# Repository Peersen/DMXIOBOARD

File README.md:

# DMXIOBOARD
PCB for DMX IO from an Arduino Nano via MAX485 or SN75176 chip

### Purpose
This PCB is is designed to use an Arduino Nano to either receive(and optionally loop through) DMX or send DMX via RS485 driverchips.

### Layout
All pins of the Arduino are accesible in the 5.08 mm pitch rows in the middle of the board.
For addressing the potential DMX device a dipswitch footprint is also provided.  
The pins used for the dipswitch are also connected to the center rows as well.

### Usage

#### Hardware
As a bare minimum an arduino nano and a RS485 driver chip are needed.
The Maxim MAX485 or Texas Instruments SN75176 are pin-identical driver chips and can be used either in a DIP8 or SO8 package on the receiving or transmitting side.
Pin one is marked by a white dot on the PCB.
The dipswitch switches its input pins to ground, so pinMode(<addrPin>, INPUT_PULLUP) should be used.
As connectors footprints for a 3-pin 5.08 mm pitch screwterminal or a XLR connector are provided.
The XLR footprint is for n Neutrik NC3MD-H (male horizontal) or a NC3FD-H (female horizontal) connector.
  
#### configuring the board

##### connecting Tx/Rx
The Tx an Rx Pins of the arduino are by default NOT connected to the driver chips and therefore nothing can be send or received.
To connect the Tx/Rx pins a solder bridge or a jumper header must be soldered on the board.
This was done because having those pins connected to the driver chips prohibits uploading a sketch.

##### configuring the output
The XLR female connector and the corresponding screwterminal can be either DMX output from the arduino or passing through the dmx input.
To decide what is does two more jumperpads most be soldered. They are labeled (solder fort XLR f = DMX Through/DMXOUT".

#### Design files
The Project was done using Kicad 6.0. You`ll find a Gerber folder in the Projekt folder that should be accepted by JLCPCB.com and other manufacturers.

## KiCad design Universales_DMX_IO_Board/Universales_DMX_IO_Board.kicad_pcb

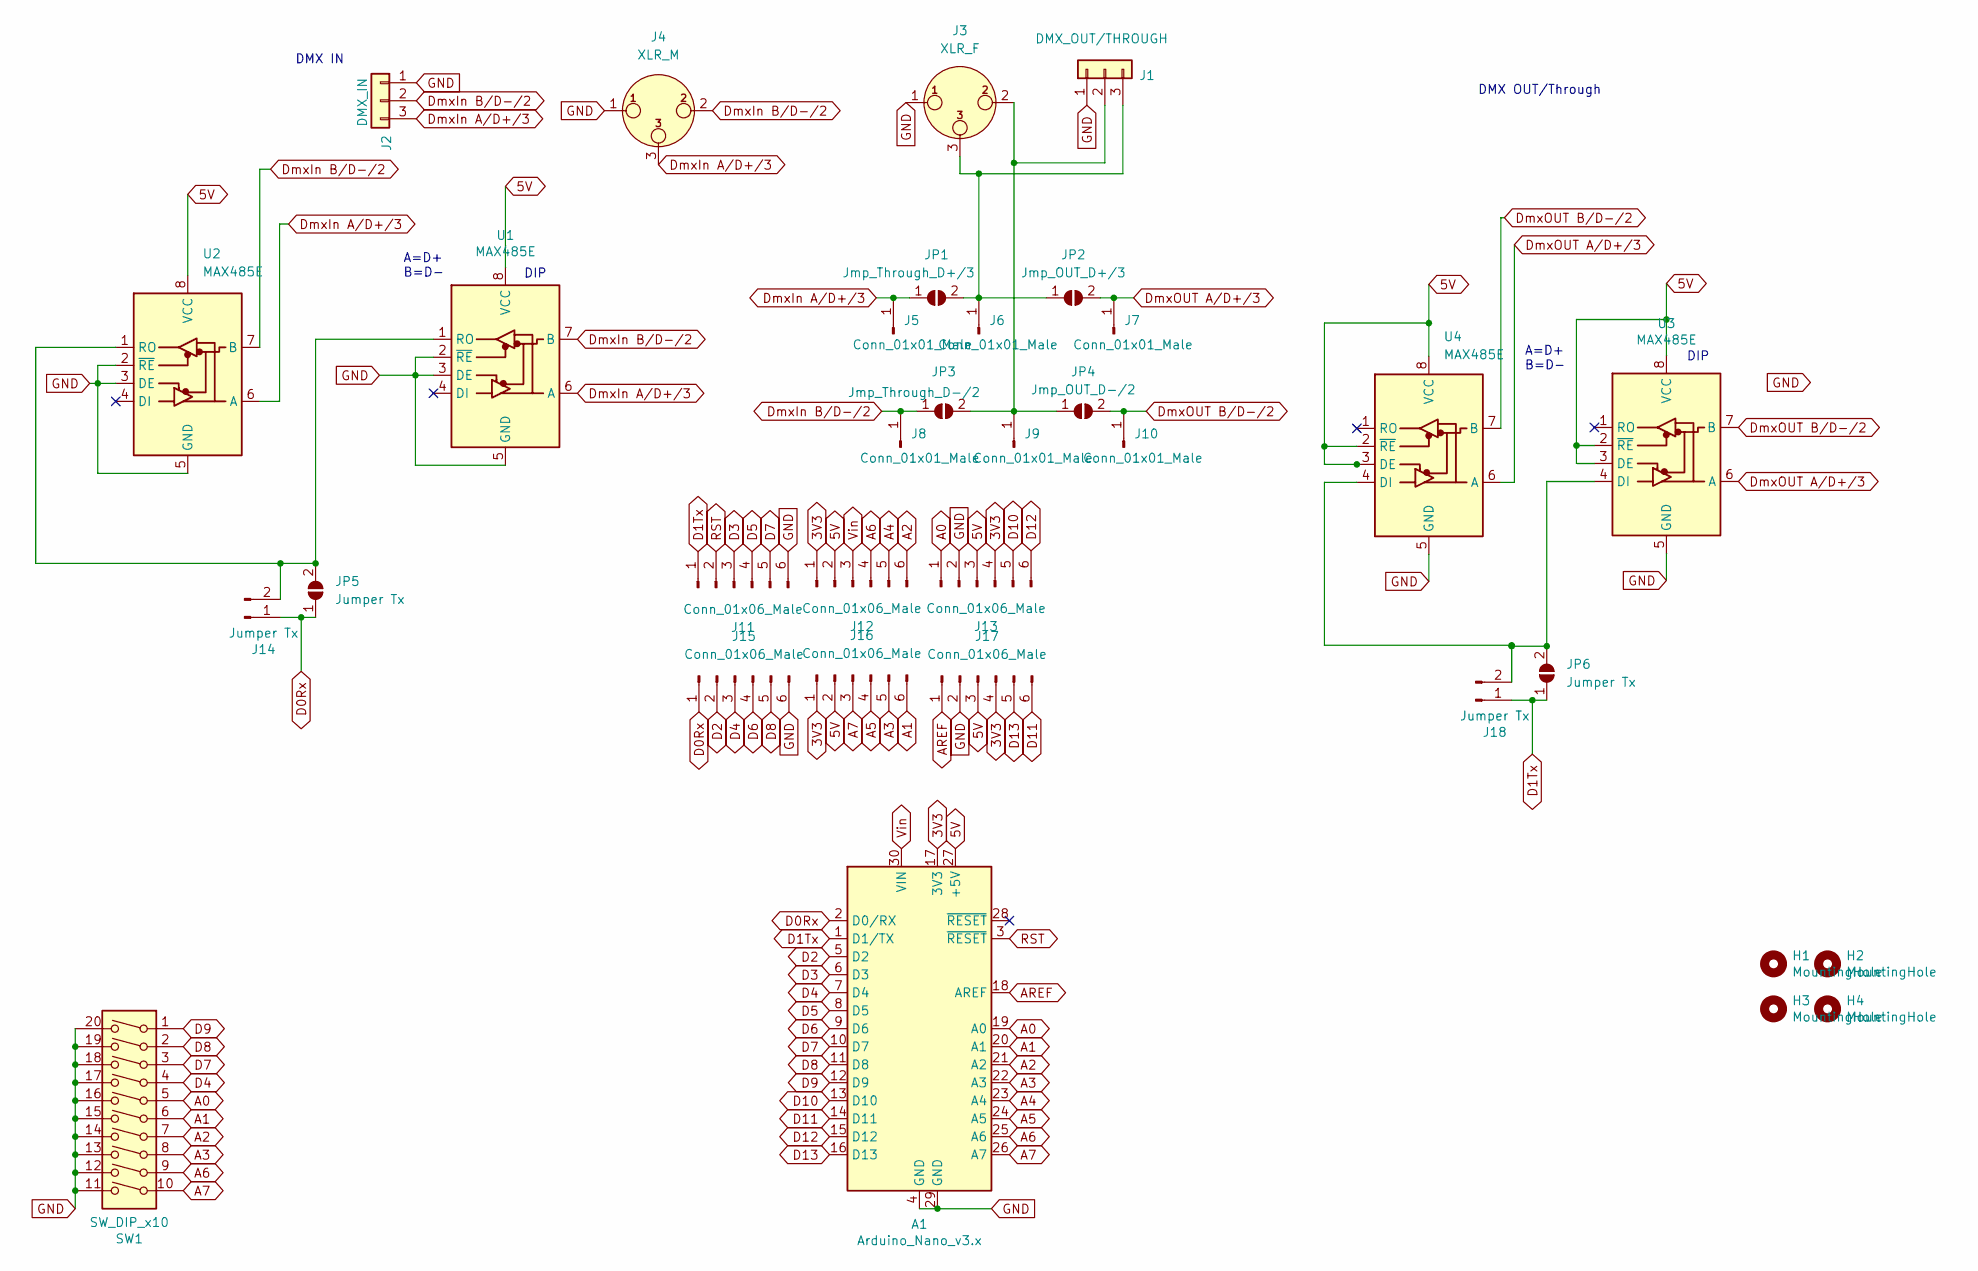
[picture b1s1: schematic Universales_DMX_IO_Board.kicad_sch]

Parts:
A1: Arduino_Nano_v3.x; Arduino_Nano_Peer_Big_Pads
H1, H2, H3, H4: MountingHole; MountingHole_3.2mm_M3_DIN965_Pad
J1: DMX_OUT/THROUGH; TerminalBlock_bornier-3_P5.08mm
J2: DMX_IN; TerminalBlock_bornier-3_P5.08mm
J3: XLR_F; Jack_XLR_Neutrik_NC3FD-H_Horizontal
J4: XLR_M; Jack_XLR_Neutrik_NC3MD-H_Horizontal
J5, J6, J7, J8, J9, J10: Conn_01x01_Male; PinHeader_1x01_P2.54mm_Vertical
J11, J12, J13, J15, J16, J17: Conn_01x06_Male; TerminalBlock_bornier-6_P5.08mm
J14, J18: Jumper Tx; PinHeader_1x02_P2.54mm_Vertical
JP1: Jmp_Through_D+/3; SolderJumper-2_P1.3mm_Open_Pad1.0x1.5mm
JP2: Jmp_OUT_D+/3; SolderJumper-2_P1.3mm_Open_Pad1.0x1.5mm
JP3: Jmp_Through_D-/2; SolderJumper-2_P1.3mm_Open_Pad1.0x1.5mm
JP4: Jmp_OUT_D-/2; SolderJumper-2_P1.3mm_Open_Pad1.0x1.5mm
JP5, JP6: Jumper Tx; SolderJumper-2_P1.3mm_Open_Pad1.0x1.5mm
SW1: SW_DIP_x10; SW_DIP_SPSTx10_Slide_9.78x27.58mm_W7.62mm_P2.54mm
U1, U3: MAX485E; SO-8_5.3x6.2mm_P1.27mm
U2, U4: MAX485E; DIP-8_W7.62mm_LongPads

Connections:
3V3: A1.17 (3V3), J12.1, J13.4, J16.1, J17.4
5V: A1.27 (+5V), J12.2, J13.3, J16.2, J17.3, U1.8 (VCC), U2.8 (VCC), U3.2 (~RE), U3.3 (DE), U3.8 (VCC), U4.2 (~RE), U4.3 (DE), U4.8 (VCC)
A0: A1.19 (A0), J13.1, SW1.5
A1: A1.20 (A1), J16.6, SW1.6
A2: A1.21 (A2), J12.6, SW1.7
A3: A1.22 (A3), J16.5, SW1.8
A4: A1.23 (A4), J12.5
A5: A1.24 (A5), J16.4
A6: A1.25 (A6), J12.4, SW1.9
A7: A1.26 (A7), J16.3, SW1.10
AREF: A1.18 (AREF), J17.1
D0Rx: A1.2 (D0/RX), J14.1, J15.1, JP5.1 (A)
D1Tx: A1.1 (D1/TX), J11.1, J18.1, JP6.1 (A)
D2: A1.5 (D2), J15.2
D3: A1.6 (D3), J11.3
D4: A1.7 (D4), J15.3, SW1.4
D5: A1.8 (D5), J11.4
D6: A1.9 (D6), J15.4
D7: A1.10 (D7), J11.5, SW1.3
D8: A1.11 (D8), J15.5, SW1.2
D9: A1.12 (D9), SW1.1
D10: A1.13 (D10), J13.5
D11: A1.14 (D11), J17.6
D12: A1.15 (D12), J13.6
D13: A1.16 (D13), J17.5
DmxIn A/D+/3: J2.3, J4.3, J5.1, JP1.1 (A), U1.6 (A), U2.6 (A)
DmxIn B/D-/2: J2.2, J4.2, J8.1, JP3.1 (A), U1.7 (B), U2.7 (B)
DmxOUT A/D+/3: J7.1, JP2.2 (B), U3.6 (A), U4.6 (A)
DmxOUT B/D-/2: J10.1, JP4.2 (B), U3.7 (B), U4.7 (B)
GND: A1.4 (GND), A1.29 (GND), J1.1, J2.1, J3.1, J4.1, J11.6, J13.2, J15.6, J17.2, SW1.11, SW1.12, SW1.13, SW1.14, SW1.15, SW1.16, SW1.17, SW1.18, SW1.19, SW1.20, U1.2 (~RE), U1.3 (DE), U1.5 (GND), U2.2 (~RE), U2.3 (DE), U2.5 (GND), U3.5 (GND), U4.5 (GND)
unnamed: J1.2, J3.2, J9.1, JP3.2 (B), JP4.1 (A)
unnamed: J1.3, J3.3, J6.1, JP1.2 (B), JP2.1 (A)
unnamed: J14.2, JP5.2 (B), U1.1 (RO), U2.1 (RO)
unnamed: J18.2, JP6.2 (B), U3.4 (DI), U4.4 (DI)
RST: A1.3 (~RESET), J11.2
Vin: A1.30 (VIN), J12.3

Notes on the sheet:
DIP
DMX IN
A=D+ B=D-
DMX OUT/Through

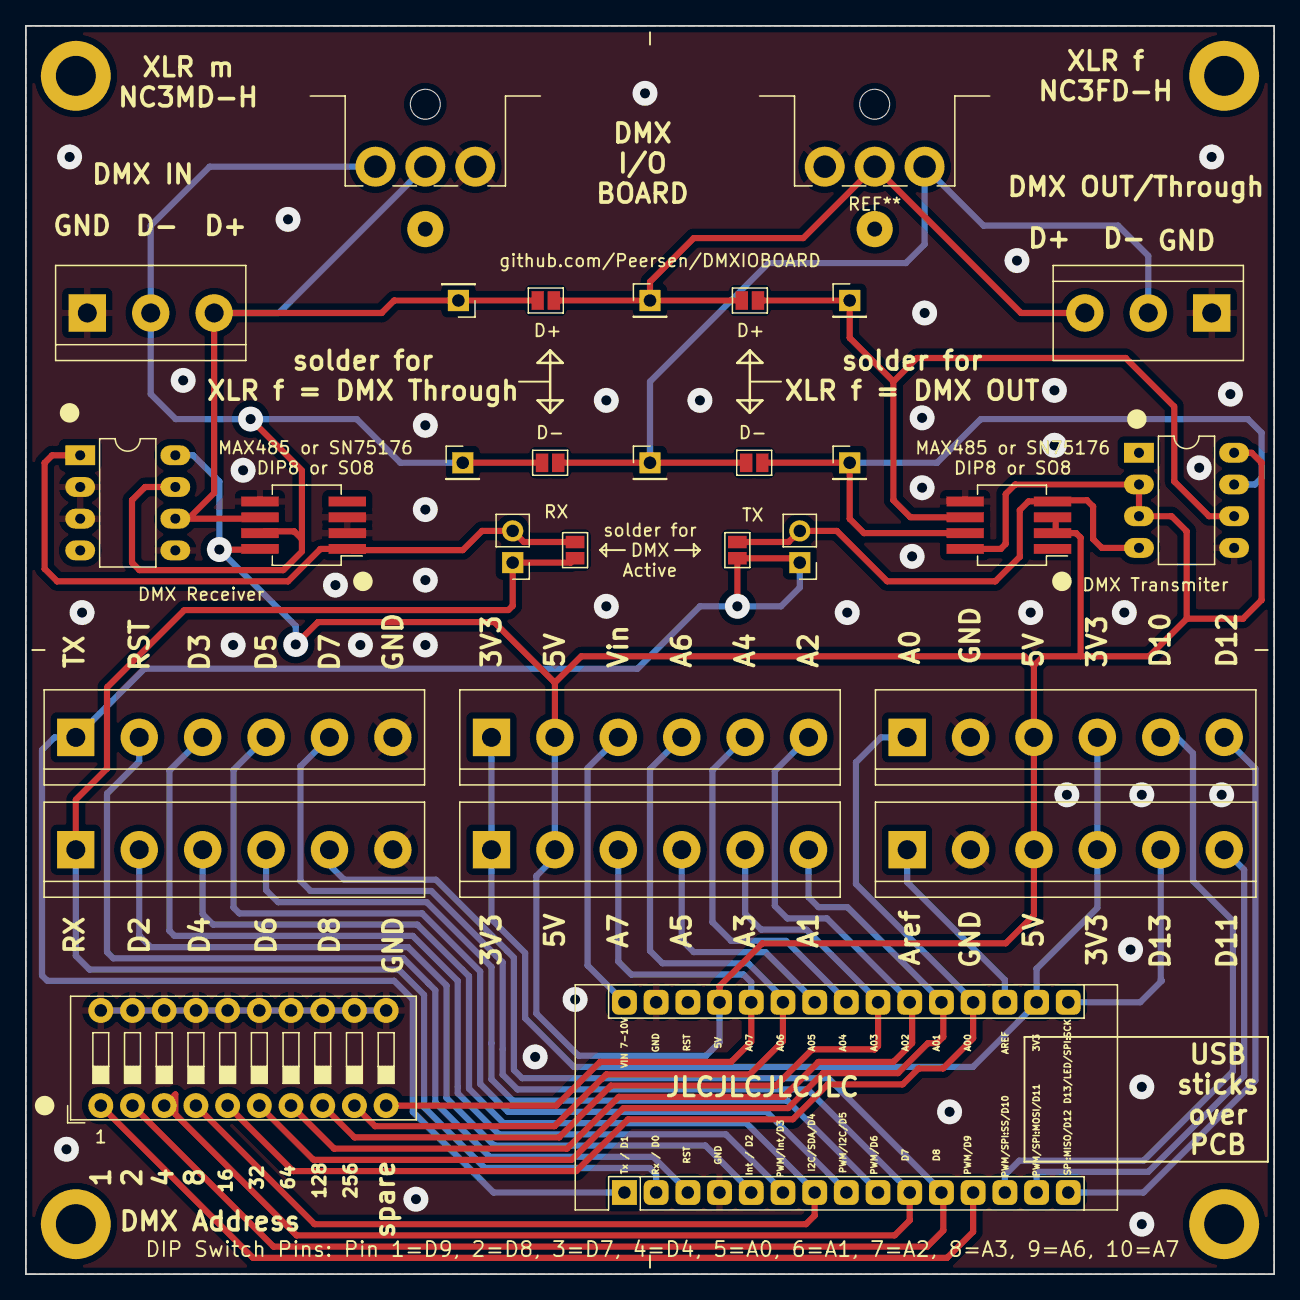
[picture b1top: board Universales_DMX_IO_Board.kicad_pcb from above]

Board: 2 copper layers, 100.0 x 100.0 mm, 34 parts (0 on the bottom side), 36 nets.
